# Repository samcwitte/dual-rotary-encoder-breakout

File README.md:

# dual-rotary-encoder-breakout
This is an open-source breakout PCB for the Bourns Inc. PEC11D-4120F-S0015 dual rotary encoder with switch.

This was made in KiCad 9.0.

All hardware and associated files are under the CERN Open Hardware Licence Version 2 - Permissive license.

All software and associated files are under the MIT license.

## Bill of Materials
Everything you'll need to make one yourself!

Alternative interactive BOM in `./ibom.html`

|   | References                         | Value              | Footprint                         | Quantity |
|---|------------------------------------|--------------------|-----------------------------------|----------|
| 1 | R1, R2, R3, R4, R5, R6, R7, R8, R9 | 10K                | 0603 (1608 Metric)                | 9        |
| 2 | C1, C2, C3, C4                     | 0.01u              | 0603 (1608 Metric)                | 4        |
| 3 | S1                                 | PEC11D-4120F-S0015 | PEC11D-4120F-S0015 Rotary Encoder | 1        |
| 4 | J3                                 | PINHD_1x7_Male     | 2.54mm pitch header               | 1        |

## Software Example

I used [Mike Teachman's micropython-rotary library](https://github.com/miketeachman/micropython-rotary) for some micropython code to run on a Raspberry Pi Pico.

You can find example code in `./software`. Be sure to use the latest version of Mike's library.

## 3D Render

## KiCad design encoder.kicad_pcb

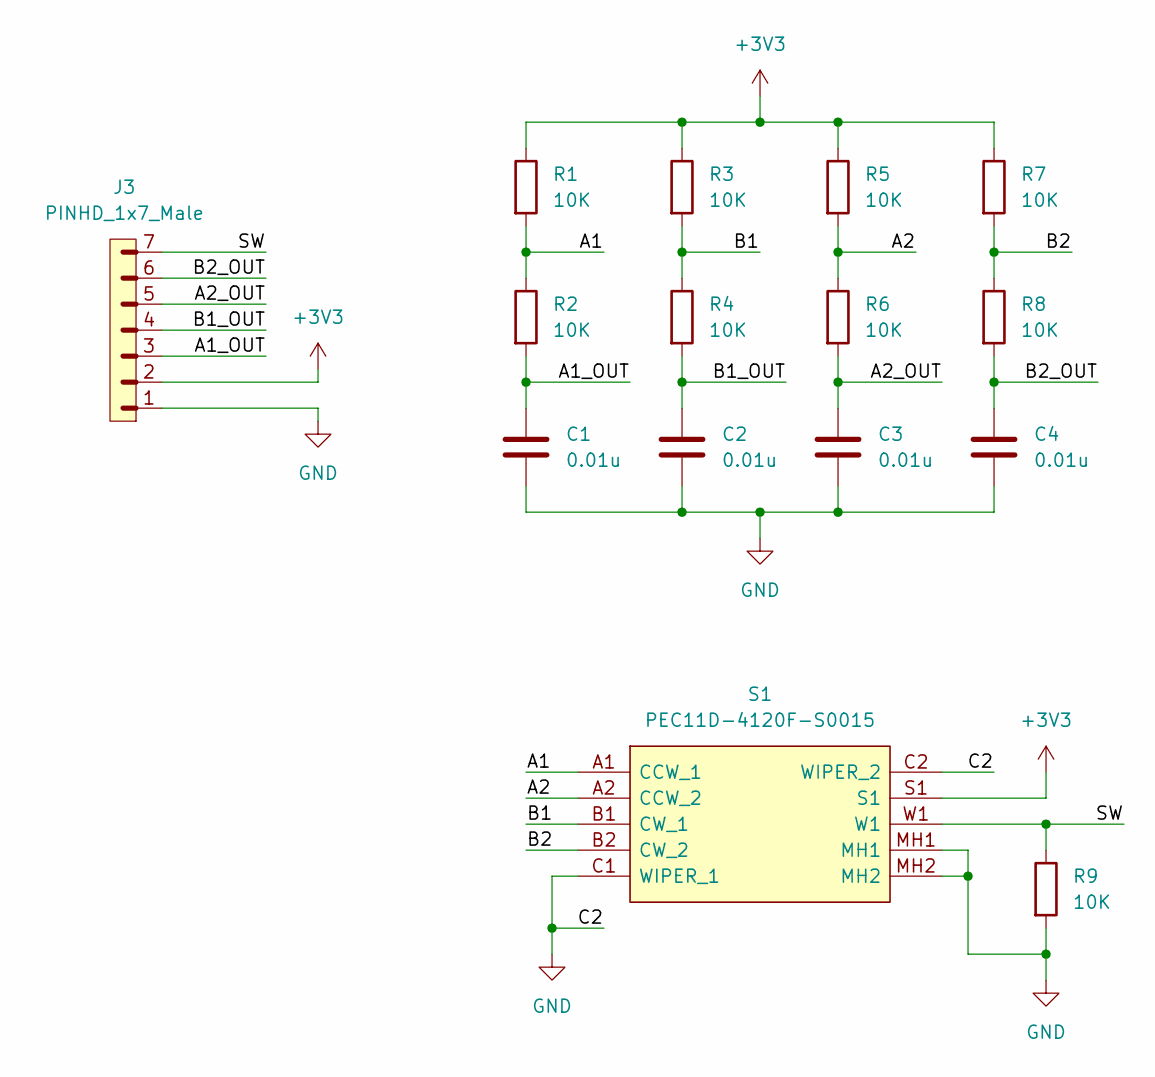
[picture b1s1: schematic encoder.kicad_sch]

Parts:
C1, C2, C3, C4: 0.01u; C_0603_1608Metric_Pad1.08x0.95mm_HandSolder; Part Number CL10B103KB8NNNC
J3: PINHD_1x7_Male; PinHeader_1x07_P2.54mm_Vertical
R1, R2, R3, R4, R5, R6, R7, R8, R9: 10K; R_0603_1608Metric_Pad0.98x0.95mm_HandSolder; Part Number AC0603FR-1310KL
S1: PEC11D-4120F-S0015; PEC11D-4120F-S0015 Rotary Encoder; Mouser Part Number 652-PEC11D4120FS0015

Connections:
+3V3: J3.2, R1.1, R3.1, R5.1, R7.1, S1.S1
/A1: R1.2, R2.1, S1.A1 (CCW_1)
/A1_OUT: C1.1, J3.3, R2.2
/A2: R5.2, R6.1, S1.A2 (CCW_2)
/A2_OUT: C3.1, J3.5, R6.2
/B1: R3.2, R4.1, S1.B1 (CW_1)
/B1_OUT: C2.1, J3.4, R4.2
/B2: R7.2, R8.1, S1.B2 (CW_2)
/B2_OUT: C4.1, J3.6, R8.2
/SW: J3.7, R9.1, S1.W1
GND: C1.2, C2.2, C3.2, C4.2, J3.1, R9.2, S1.C1 (WIPER_1), S1.C2 (WIPER_2), S1.MH1, S1.MH2

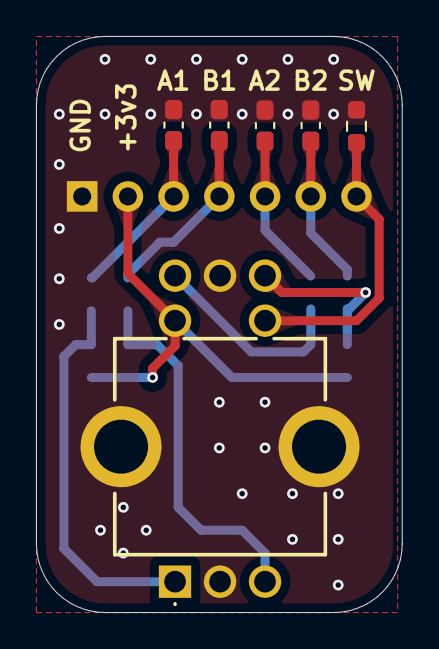
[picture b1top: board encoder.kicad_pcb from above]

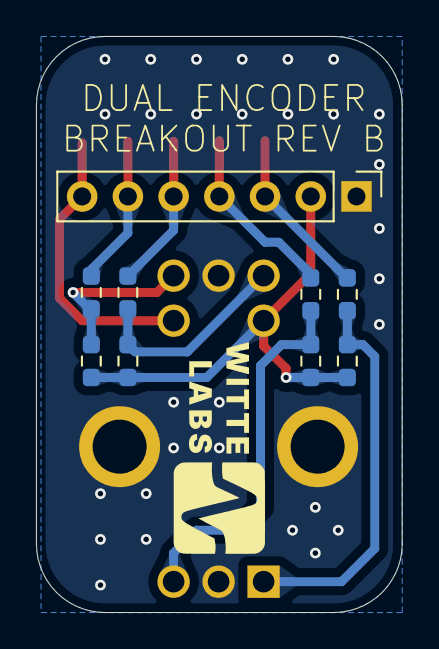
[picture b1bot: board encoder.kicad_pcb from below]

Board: 2 copper layers, 20.3 x 32.0 mm, 15 parts (9 on the bottom side), 11 nets.

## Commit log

2026-02-11 added KiCad files and interactive .html BOM
2026-02-11 Added example micropython script and supporting libraries, as well as MIT license for software
2026-02-11 Update README.md
    Oops... left a line in there on accident. Removed it.
